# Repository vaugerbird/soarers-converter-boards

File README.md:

# Soarers-Dongle

Like the description says, this is just a simple dongle adapter for converting an IBM Model M with RJ45 plug to USB through various methods. I whiped up the PCBs in about an hour each, so there might be errors in the PCB design. If there is, file an issue report and I'll fix it right away! Also, please do not plug an ethernet cord into the dongle or keypad, as it might do weird things (or nothing at all)! 

<br>

I've included the EAGLE PCB files for all of the boards, their respective BOMs, and all of Soarer's files relevent to the PCBs. I <i><b>in no way take</b></i> responsibity for creating or modifying the files in the soarers-files folder, all credit goes to Soarer. If you want more info on the original project, check out Soarer's guide [here](https://deskthority.net/viewtopic.php?f=7&t=2510&start=).

TODO
------
To view what needs to be done and what has been done, check out my [Trello](https://trello.com/b/eKjTxFPa/soarers-converter-boards) board!

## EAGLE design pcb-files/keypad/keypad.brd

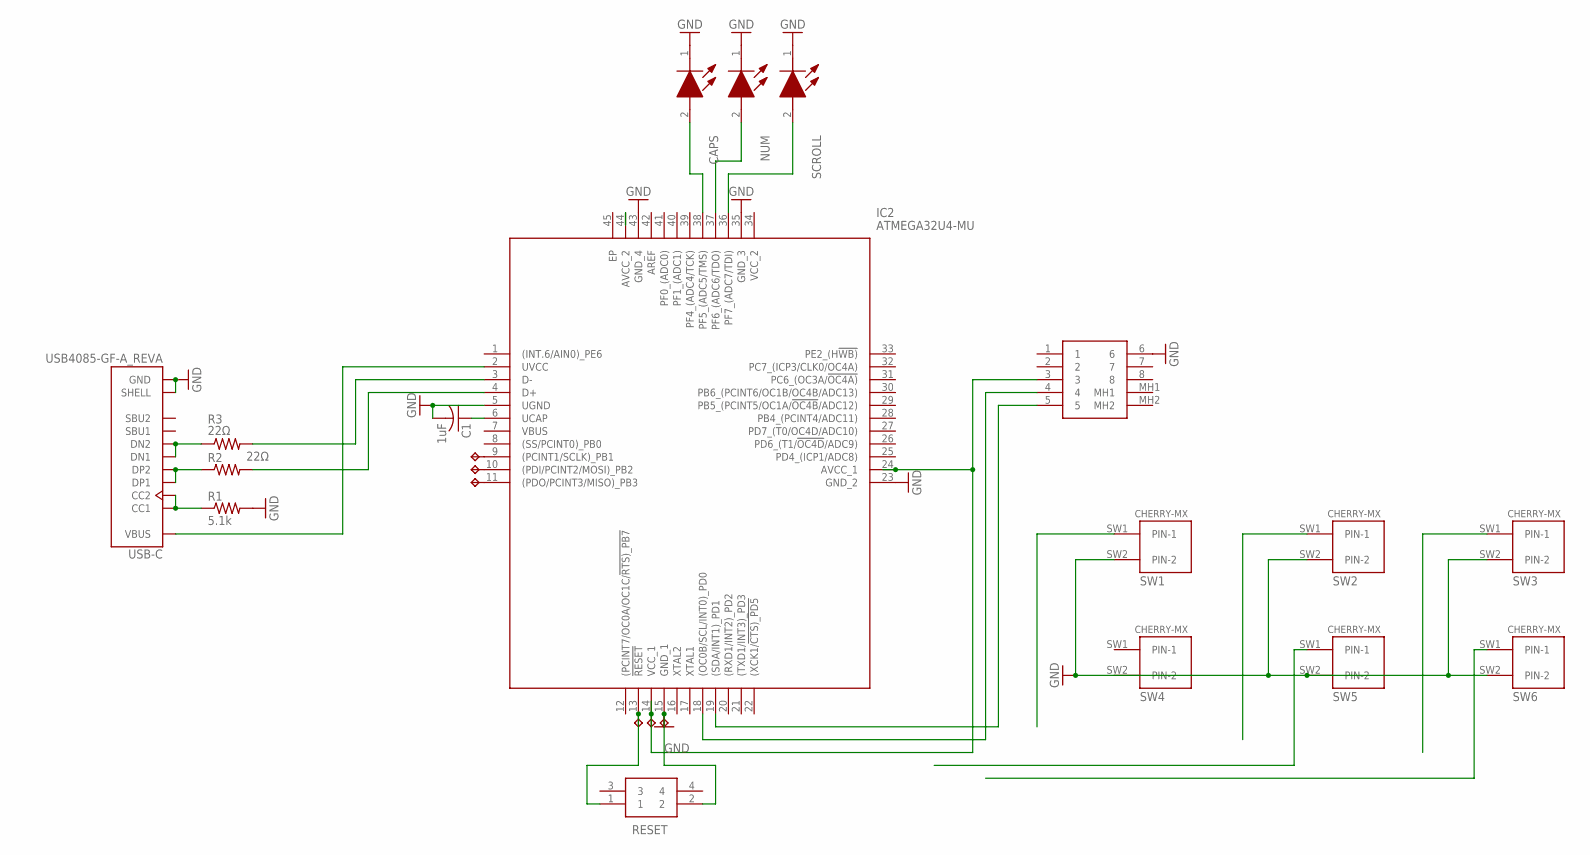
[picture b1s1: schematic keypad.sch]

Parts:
5V: TPTP17R; TP17R
C1: 1uF; C0805
CAPS: 155060GS75300
GND: TPTP17R; TP17R
IC2: ATMEGA32U4-MU; QFN50P700X700X100-45N
J2: SS-60300-046; SS60300046
MISO: TPTP17R; TP17R
MOSI: TPTP17R; TP17R
NUM: 155060GS75300
R1: 5.1k; R0603
R2, R3: 22Ω; R0805
RESET: LL3303F065QG
RST: TPTP17R; TP17R
SCLK: TPTP17R; TP17R
SCROLL: 155060GS75300
SW1, SW2, SW3, SW4, SW5, SW6: CHERRY-MX
USB-C: USB4085-GF-A_REVA; GCT_USB4085-GF-A_REVA

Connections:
CAPS: CAPS.2 (A), IC2.38 (PF5_(ADC5/TMS))
CC: R1.1, USB-C.A5 (CC1), USB-C.B5 (CC2)
CLK: IC2.19 ((SDA/INT1)_PD1), J2.5
D+: R2.1, USB-C.A6 (DP1), USB-C.B6 (DP2)
D+RES: IC2.4 (D+), R2.2
D-: R3.1, USB-C.A7 (DN1), USB-C.B7 (DN2)
D-RES: IC2.3 (D-), R3.2
DATA: IC2.18 ((OC0B/SCL/INT0)_PD0), J2.4
GND: C1.2, CAPS.1 (K), GND.TP, IC2.5 (UGND), IC2.15 (GND_1), IC2.23 (GND_2), IC2.35 (GND_3), IC2.43 (GND_4), J2.6, NUM.1 (K), R1.2, RESET.2, SCROLL.1 (K), SW1.SW2 (PIN-2), SW2.SW2 (PIN-2), SW3.SW2 (PIN-2), SW4.SW2 (PIN-2), SW5.SW2 (PIN-2), SW6.SW2 (PIN-2), USB-C.A1 (GND), USB-C.A12 (GND), USB-C.B1 (GND), USB-C.B12 (GND), USB-C.P1 (SHELL), USB-C.P2 (SHELL), USB-C.P3 (SHELL), USB-C.P4 (SHELL)
MISO: IC2.11 ((PDO/PCINT3/MISO)_PB3), MISO.TP
MOSI: IC2.10 ((PDI/PCINT2/MOSI)_PB2), MOSI.TP
NUM: IC2.37 (PF6_(ADC6/TDO)), NUM.2 (A)
RESET: IC2.13 (!RESET), RESET.1, RST.TP
SCLK: IC2.9 ((PCINT1/SCLK)_PB1), SCLK.TP
SCRL: IC2.36 (PF7_(ADC7/TDI)), SCROLL.2 (A)
SW1: SW1.SW1 (PIN-1)
SW2: SW2.SW1 (PIN-1)
SW3: SW3.SW1 (PIN-1)
SW5: SW5.SW1 (PIN-1)
SW6: SW6.SW1 (PIN-1)
UCAP: C1.1, IC2.6 (UCAP)
VCC: 5V.TP, IC2.14 (VCC_1), IC2.24 (AVCC_1), IC2.44 (AVCC_2), J2.3
VIN: IC2.2 (UVCC), USB-C.A4 (VBUS), USB-C.A9 (VBUS), USB-C.B4 (VBUS), USB-C.B9 (VBUS)

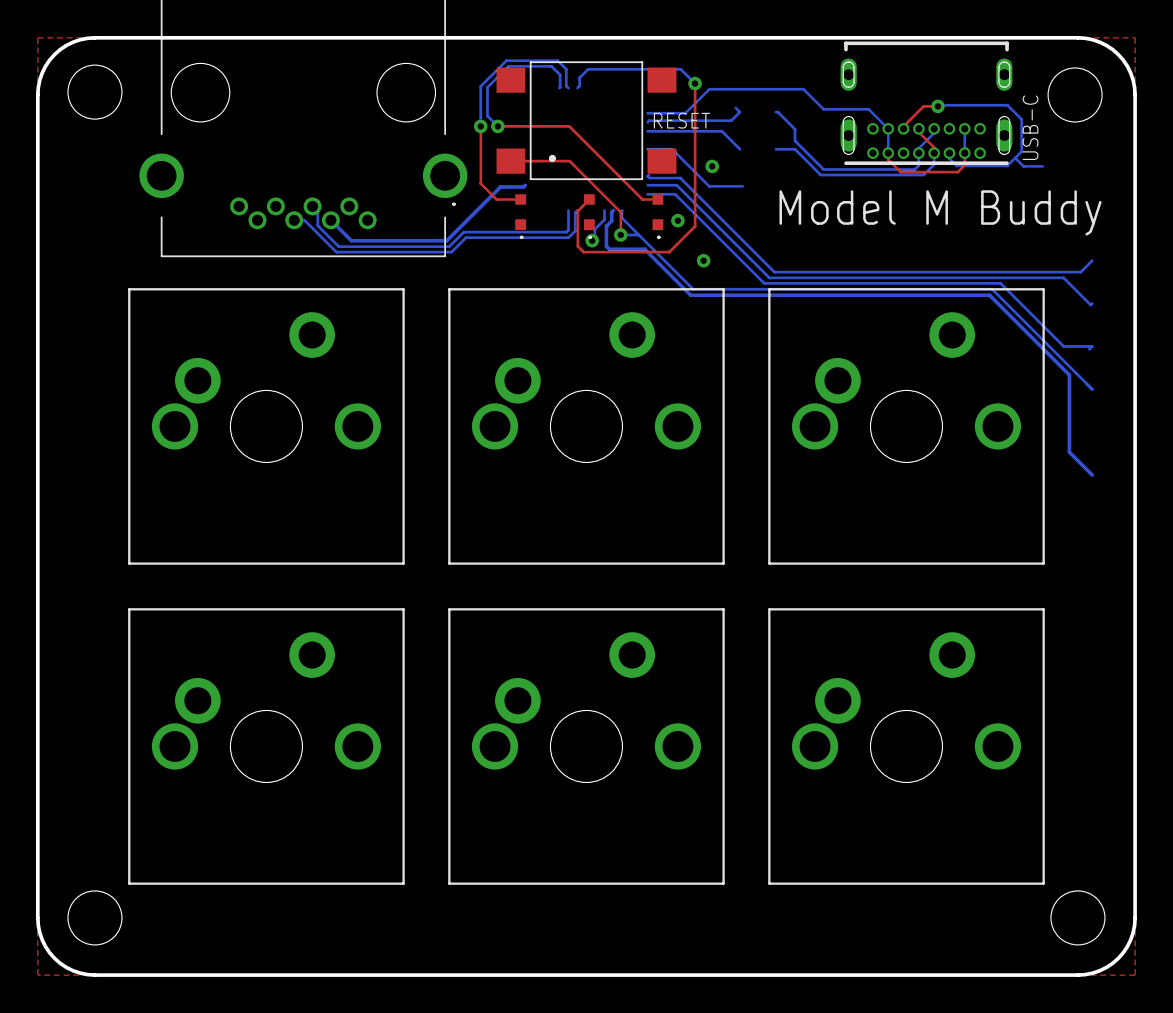
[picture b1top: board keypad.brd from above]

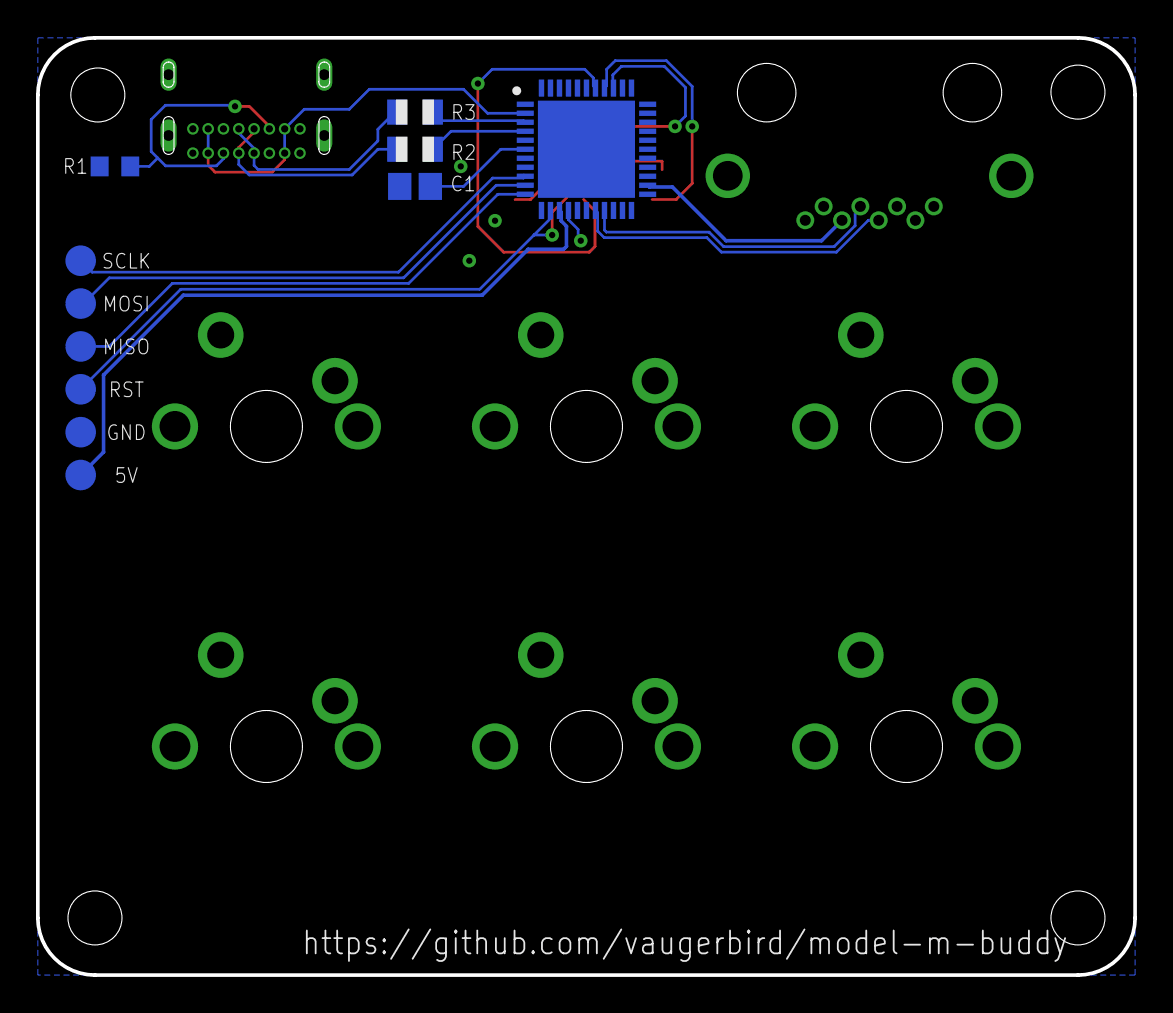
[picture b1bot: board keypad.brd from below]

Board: 2 copper layers, 61.0 x 52.1 mm, 23 parts (11 on the bottom side), 18 nets.

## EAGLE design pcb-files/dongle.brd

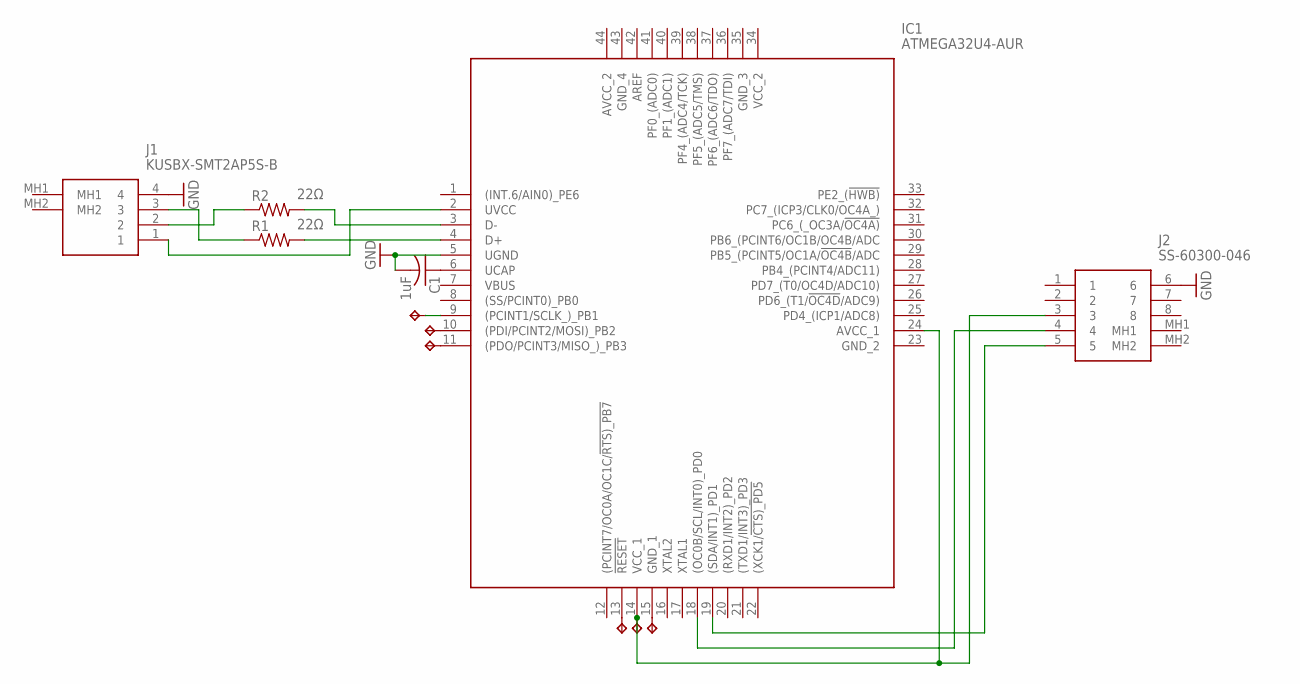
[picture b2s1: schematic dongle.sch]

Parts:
5V: TPTP17R; TP17R
C1: 1uF; C0805
GND: TPTP17R; TP17R
IC1: ATMEGA32U4-AUR; QFP80P1200X1200X120-44N
J1: KUSBX-SMT2AP5S-B; KUSBXSMT2AP5SB
J2: SS-60300-046; SS60300046
MISO: TPTP17R; TP17R
MOSI: TPTP17R; TP17R
R1, R2: 22Ω; R0805
RST: TPTP17R; TP17R
SCLK: TPTP17R; TP17R

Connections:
CLK: IC1.19 ((SDA/INT1)_PD1), J2.5
D+: J1.3, R1.1
D+RES: IC1.4 (D+), R1.2
D-: J1.2, R2.1
D-RES: IC1.3 (D-), R2.2
DATA: IC1.18 ((OC0B/SCL/INT0)_PD0), J2.4
GND: C1.2, GND.TP, IC1.5 (UGND), IC1.15 (GND_1), J1.4, J2.6
MISO: IC1.11 ((PDO/PCINT3/MISO_)_PB3), MISO.TP
MOSI: IC1.10 ((PDI/PCINT2/MOSI)_PB2), MOSI.TP
RST: IC1.13 (!RESET), RST.TP
SCLK: IC1.9 ((PCINT1/SCLK_)_PB1), SCLK.TP
UCAP: C1.1, IC1.6 (UCAP)
VCC: 5V.TP, IC1.14 (VCC_1), IC1.24 (AVCC_1), J2.3
VIN: IC1.2 (UVCC), J1.1

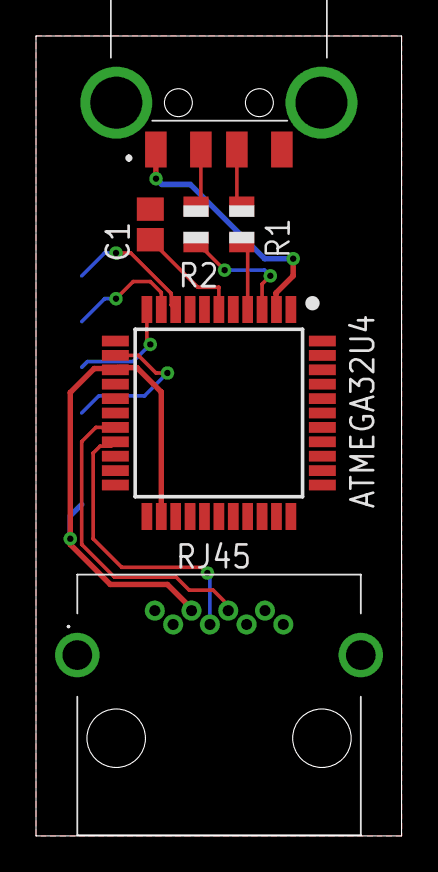
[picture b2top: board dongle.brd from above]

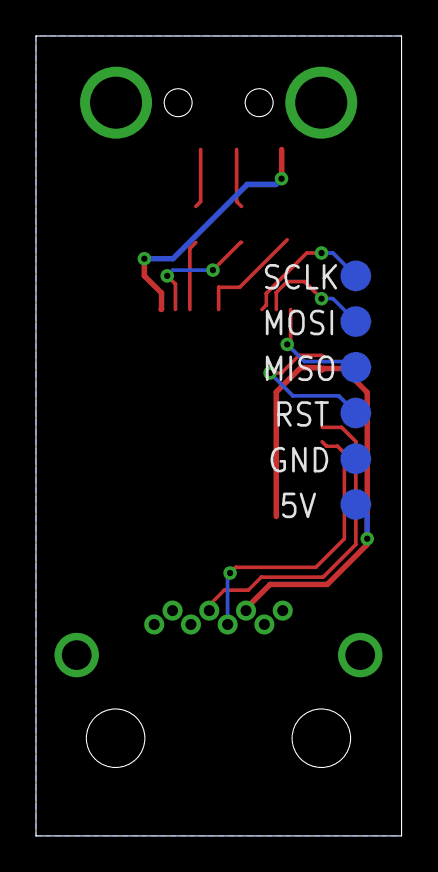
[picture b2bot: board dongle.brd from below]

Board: 2 copper layers, 20.3 x 44.4 mm, 12 parts (6 on the bottom side), 14 nets.

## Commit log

2020-12-20 Add all files from Soarer
2020-12-20 Create PCB files and BOM
2020-12-20 Add finished PCB and BOM
2020-12-20 Make Gerber
2020-12-20 Clean up unneeded files
2020-12-20 Update PCB with better USB placement
2020-12-20 Update PCB
2020-12-23 Add batch firmware installer
2021-01-07 Fix BOM
2021-03-08 Combine model-m-buddy and soarers-dongle
2021-03-08 Workin on the implant
2021-03-09 Finishing touches on implant + gerber
2021-03-09 Just some renaming
2021-03-10 Finished the last board design
